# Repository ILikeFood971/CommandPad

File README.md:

# CommandPad  

Mechanical macropad utilizing the Seeed XIAO RP2040. Has 9 keys plus two rotary encoders, an OLED display, and sk6812 mini-e leds under each key.
CommandPad uses kmk firmware and an optional companion app that allows the OLED display to include information about volume and song titles.

## CAD

There are three 3D printed pieces that fits together using M3 bolts and heatset inserts. The bottom piece holds the pcb, the middle holds the switches, and the top makes it look nice. There is a hole on the back side for a usb plug to utilize CommandPad. The snowboarder sillouette is featured since snowboarding is cool. The case was fully designed in Fusion360. The PCB model was exported from KiCad as a reference.

## PCB

The PCB was designed in KiCad.

## Firmware

CommandPad uses KMK to power everything.

- The 3x3 matrix acts as customizable hotkeys currently set to f13 to f21
- The 2 rotary encoders act as a volume control and horizontal scroll wheel
    - Pressing them is by default set to f22 and f23 but it can be change to play/pause, mute, etc.
- The OLED screen stays dark until you change volume or play music with the companion app runnning. Then it will show your volume level or the title of the current song (scrolls if it is too long)

## BOM

| Item                        | Quantity | Type/Details                |
|-----------------------------|----------|-----------------------------|
| Cherry MX Switches          | 9        | Mechanical switches         |
| Blank DSA Keycaps           | 9        | Keycaps                     |
| M3x5x4 Heatset inserts      | 5        | Hardware                    |
| M3x16mm SHCS Bolts          | 5        | Hardware                    |
| 1N4148 DO-35 Diodes         | 9        | Through hole                |
| Through hole resistors      | 2        | 4.7k                        |
| Through hole capacitors     | 9        | 100nF (0.1uF)               |
| SK6812 MINI-E LEDs          | 9        | RGB LEDs                    |
| 0.91" 128x32 OLED Display   | 1        | Display                     |
| EC11 Rotary Encoder         | 2        | Rotary encoder              |
| Seeed XIAO RP2040           | 1        | Through hole                |
| MCP23017                    | 1        | Through hole                |
| 74AHCT125                   | 1        | Through hole                |
| PCB                         | 1        | Printed circuit board       |
| Case (3 printed parts)      | 1        | 3D printed enclosure        |

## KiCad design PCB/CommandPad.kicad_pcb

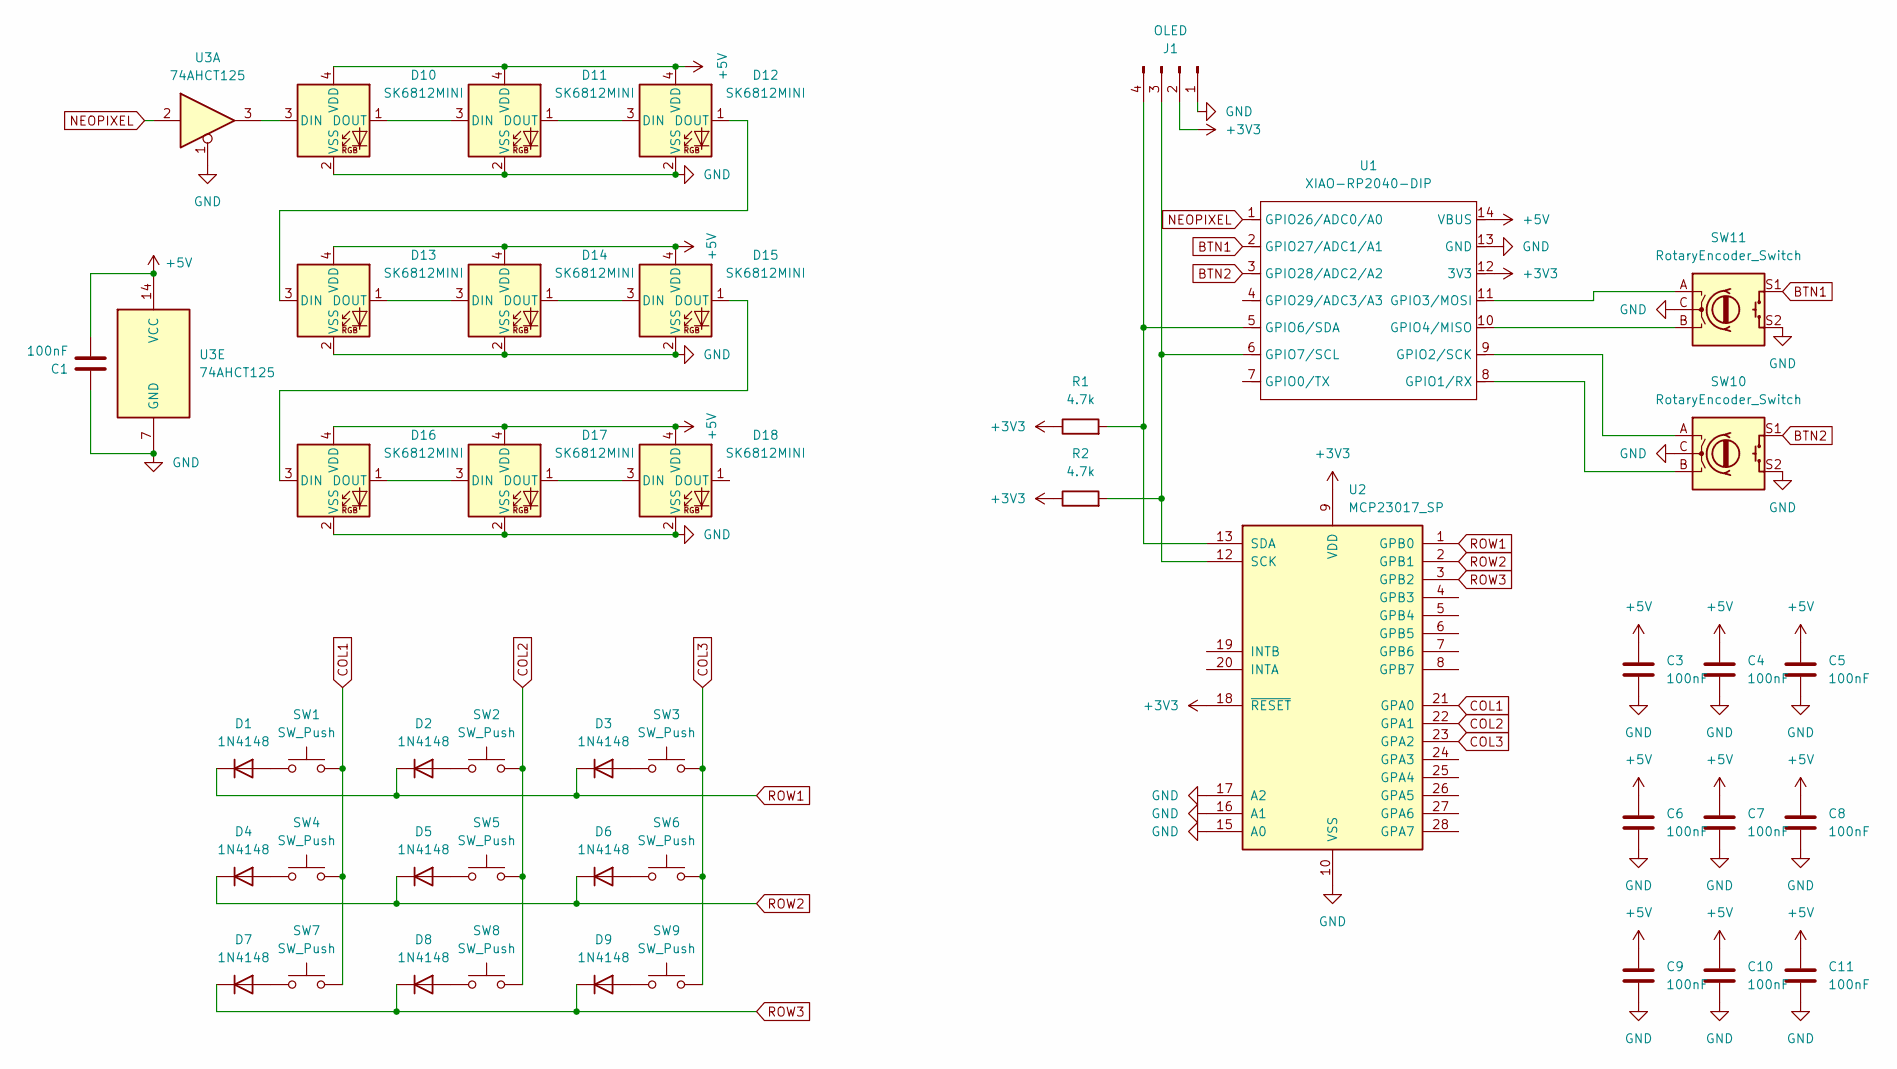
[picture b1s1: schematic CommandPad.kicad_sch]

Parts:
C1, C3, C4, C5, C6, C7, C8, C9, C10, C11: 100nF; C_Disc_D3.0mm_W1.6mm_P2.50mm
D1, D2, D3, D4, D5, D6, D7, D8, D9: 1N4148; D_DO-35_SOD27_P7.62mm_Horizontal
D10, D11, D12, D13, D14, D15, D16, D17, D18: SK6812MINI; LED_SK6812MINI
J1: OLED; SSD1306-0.91-OLED-4pin-128x32
R1, R2: 4.7k; R_Axial_DIN0207_L6.3mm_D2.5mm_P7.62mm_Horizontal
SW1, SW2, SW3, SW4, SW5, SW6, SW7, SW8, SW9: SW_Push; MX_PCB_1.00u
SW10, SW11: RotaryEncoder_Switch; Encoder_EC11_MX
U1: XIAO-RP2040-DIP
U2: MCP23017_SP; DIP-28_W7.62mm
U3: 74AHCT125; DIP-14_W7.62mm

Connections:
+3V3: J1.2, R1.1, R2.1, U1.12 (3V3), U2.9 (VDD), U2.18 (~RESET)
+5V: C1.2, C3.1, C4.1, C5.1, C6.1, C7.1, C8.1, C9.1, C10.1, C11.1, D10.4 (VDD), D11.4 (VDD), D12.4 (VDD), D13.4 (VDD), D14.4 (VDD), D15.4 (VDD), D16.4 (VDD), D17.4 (VDD), D18.4 (VDD), U1.14 (VBUS), U3.14 (VCC)
BTN1: SW11.S1, U1.2 (GPIO27/ADC1/A1)
BTN2: SW10.S1, U1.3 (GPIO28/ADC2/A2)
COL1: SW1.2, SW4.2, SW7.2, U2.21 (GPA0)
COL2: SW2.2, SW5.2, SW8.2, U2.22 (GPA1)
COL3: SW3.2, SW6.2, SW9.2, U2.23 (GPA2)
GND: C1.1, C3.2, C4.2, C5.2, C6.2, C7.2, C8.2, C9.2, C10.2, C11.2, D10.2 (VSS), D11.2 (VSS), D12.2 (VSS), D13.2 (VSS), D14.2 (VSS), D15.2 (VSS), D16.2 (VSS), D17.2 (VSS), D18.2 (VSS), J1.1, SW10.C, SW10.S2, SW11.C, SW11.S2, U1.13 (GND), U2.10 (VSS), U2.15 (A0), U2.16 (A1), U2.17 (A2), U3.1, U3.7 (GND)
NEOPIXEL: U1.1 (GPIO26/ADC0/A0), U3.2
unnamed: D1.2 (A), SW1.1
unnamed: D2.2 (A), SW2.1
unnamed: D3.2 (A), SW3.1
unnamed: D4.2 (A), SW4.1
unnamed: D5.2 (A), SW5.1
unnamed: D6.2 (A), SW6.1
unnamed: D7.2 (A), SW7.1
unnamed: D8.2 (A), SW8.1
unnamed: D9.2 (A), SW9.1
unnamed: D10.3 (DIN), U3.3
unnamed: D10.1 (DOUT), D11.3 (DIN)
unnamed: D11.1 (DOUT), D12.3 (DIN)
unnamed: D12.1 (DOUT), D13.3 (DIN)
unnamed: D13.1 (DOUT), D14.3 (DIN)
unnamed: D14.1 (DOUT), D15.3 (DIN)
unnamed: D15.1 (DOUT), D16.3 (DIN)
unnamed: D16.1 (DOUT), D17.3 (DIN)
unnamed: D17.1 (DOUT), D18.3 (DIN)
unnamed: J1.3, R2.2, U1.6 (GPIO7/SCL), U2.12 (SCK)
unnamed: J1.4, R1.2, U1.5 (GPIO6/SDA), U2.13 (SDA)
unnamed: SW10.B, U1.8 (GPIO1/RX)
unnamed: SW10.A, U1.9 (GPIO2/SCK)
unnamed: SW11.A, U1.11 (GPIO3/MOSI)
unnamed: SW11.B, U1.10 (GPIO4/MISO)
ROW1: D1.1 (K), D2.1 (K), D3.1 (K), U2.1 (GPB0)
ROW2: D4.1 (K), D5.1 (K), D6.1 (K), U2.2 (GPB1)
ROW3: D7.1 (K), D8.1 (K), D9.1 (K), U2.3 (GPB2)

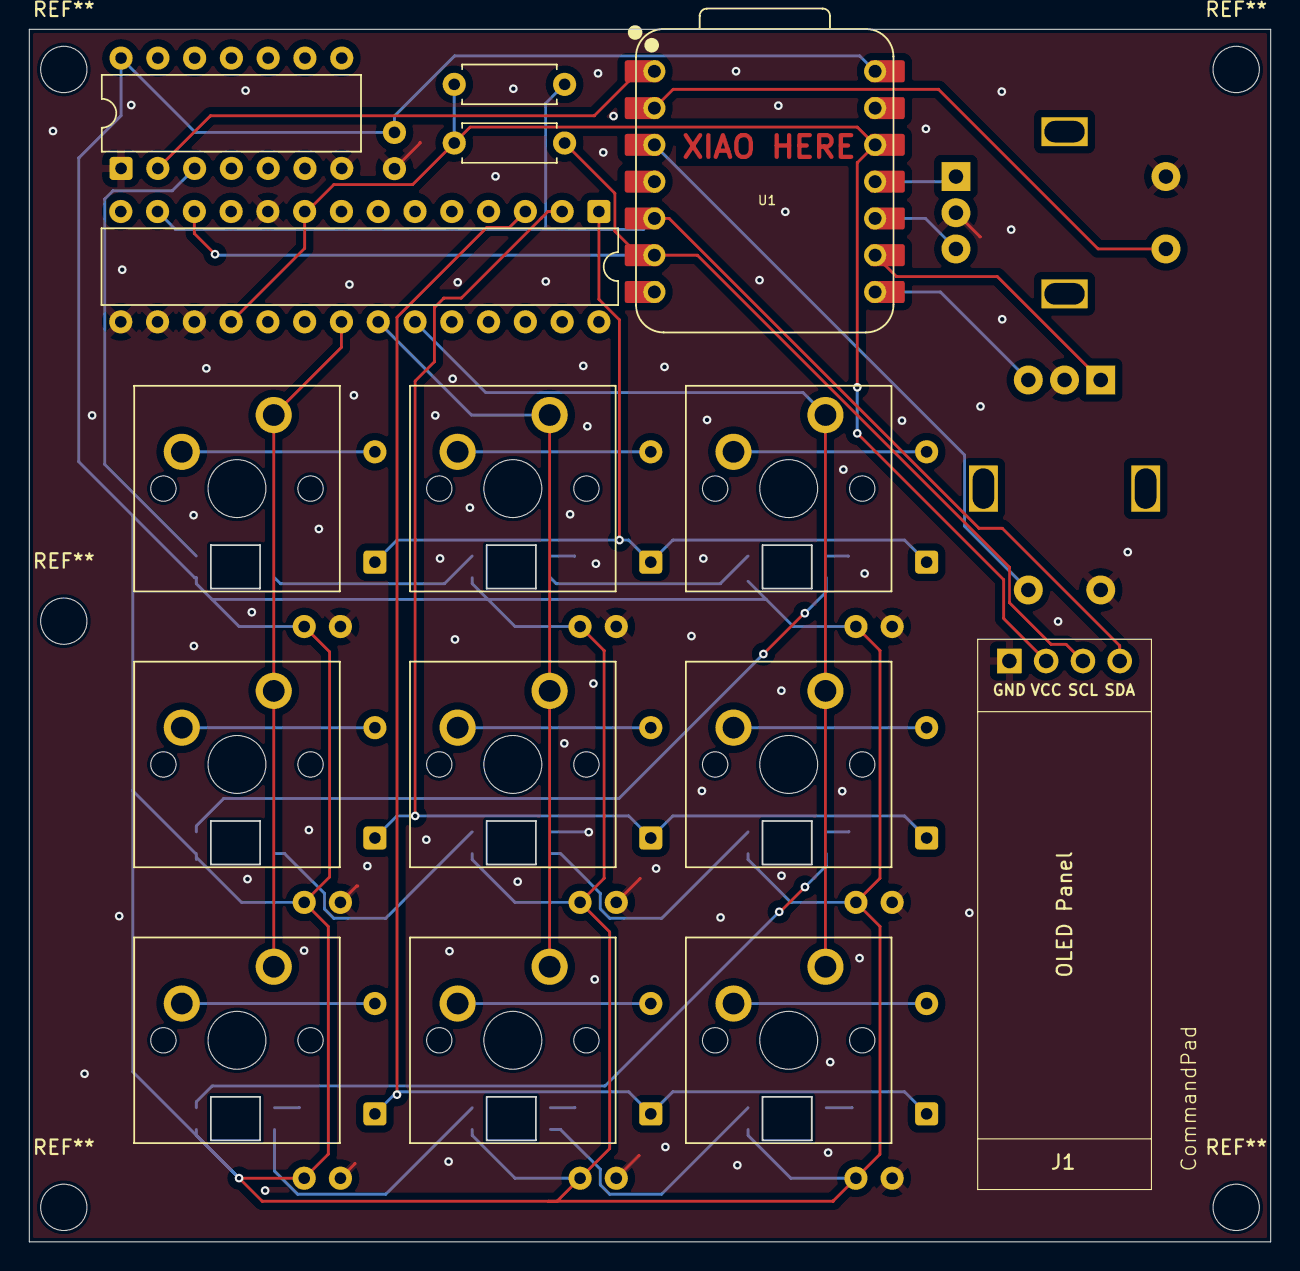
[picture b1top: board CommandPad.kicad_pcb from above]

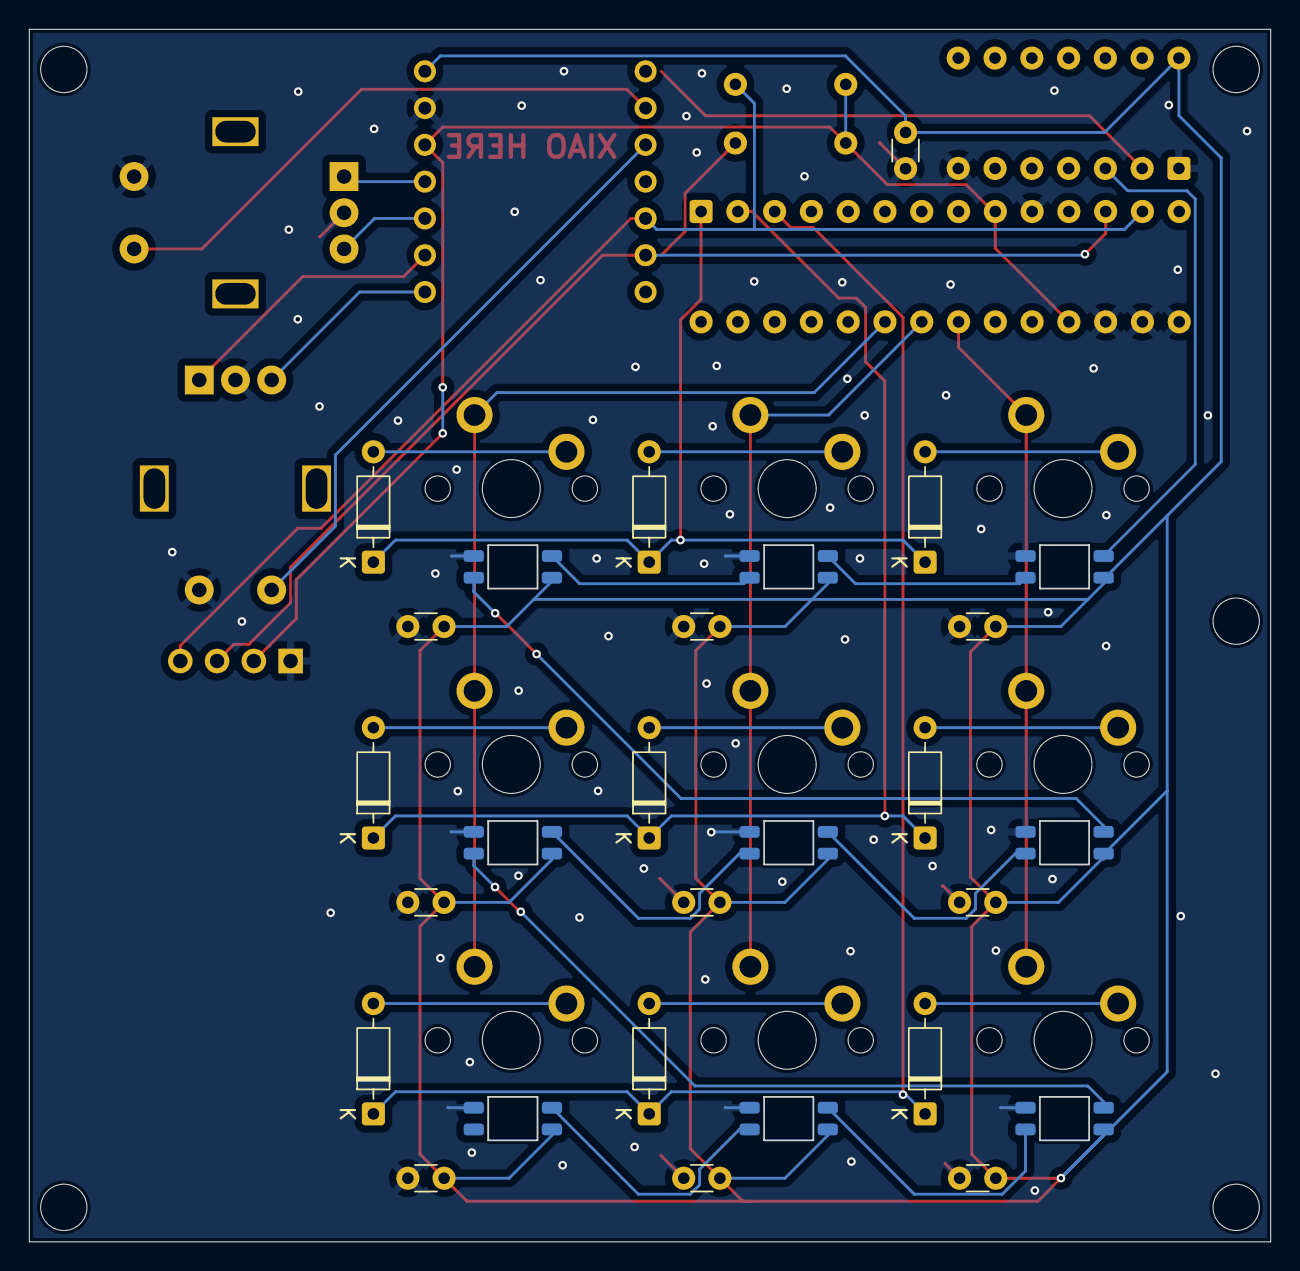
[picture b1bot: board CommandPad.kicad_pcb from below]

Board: 2 copper layers, 85.7 x 83.7 mm, 45 parts (28 on the bottom side), 36 nets.

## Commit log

2025-07-31 Add files for cad, pcb, and firmware as well as update readme
2025-07-31 Update BOM to a table format
2025-08-02 Fix incorrect pcb file
